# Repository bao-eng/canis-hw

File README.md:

# canis-hw
Isolated USB CAN-FD interface with SW-controllable termination resistors

## Features
- 2xCAN-FD interfaces supporting 8Mb/s
- 3kV isolation
- SW-controllable CAN-termination resistors
- 24V tolerant CAN transceivers and CAN termination circuit
- USB Type-C connector
- 2-layer PCB design
- Easy to solder 0603 components

## Firmware
Please use this candleLight_fw [fork](https://github.com/bao-eng/candleLight_fw/tree/canis)(canis branch). \
Prebuilt binary ```canis_fw.bin``` can be found in [releases](https://github.com/bao-eng/candleLight_fw/releases).
#### Flashing via DFU
- Short J2 pins ```1``` and ```2```
- Connect USB to the host PC
- Unshort J2
- In the ```lsusb``` output you should be able to see ```STMicroelectronics STM Device in DFU Mode```
- Run ```sudo dfu-util -d 0483:df11 -c 1 -i 0 -a 0 -s 0x08000000 -D canis_fw.bin```
- Reconnect USB
- In the ```lsusb``` output you should be able to see ```OpenMoko, Inc. Geschwister Schneider CAN adapter```
#### Flashing via SWD
- Connect ST-link to the J2
- Connect USB to the host PC
- Run ```st-flash write canis_fw.bin 0x08000000```
- Disconnect ST-link from J2
- Reconnect USB
- In the ```lsusb``` output you should be able to see ```OpenMoko, Inc. Geschwister Schneider CAN adapter```
## Usage
Bring up can0 interface and enable 120Ohm termination resistor:
```
ip link set can0 up type can bitrate 1000000 dbitrate 8000000 fd on termination 120
```
Disable 120Ohm termination resistor:
```
ip link set can0 type can termination 0
```

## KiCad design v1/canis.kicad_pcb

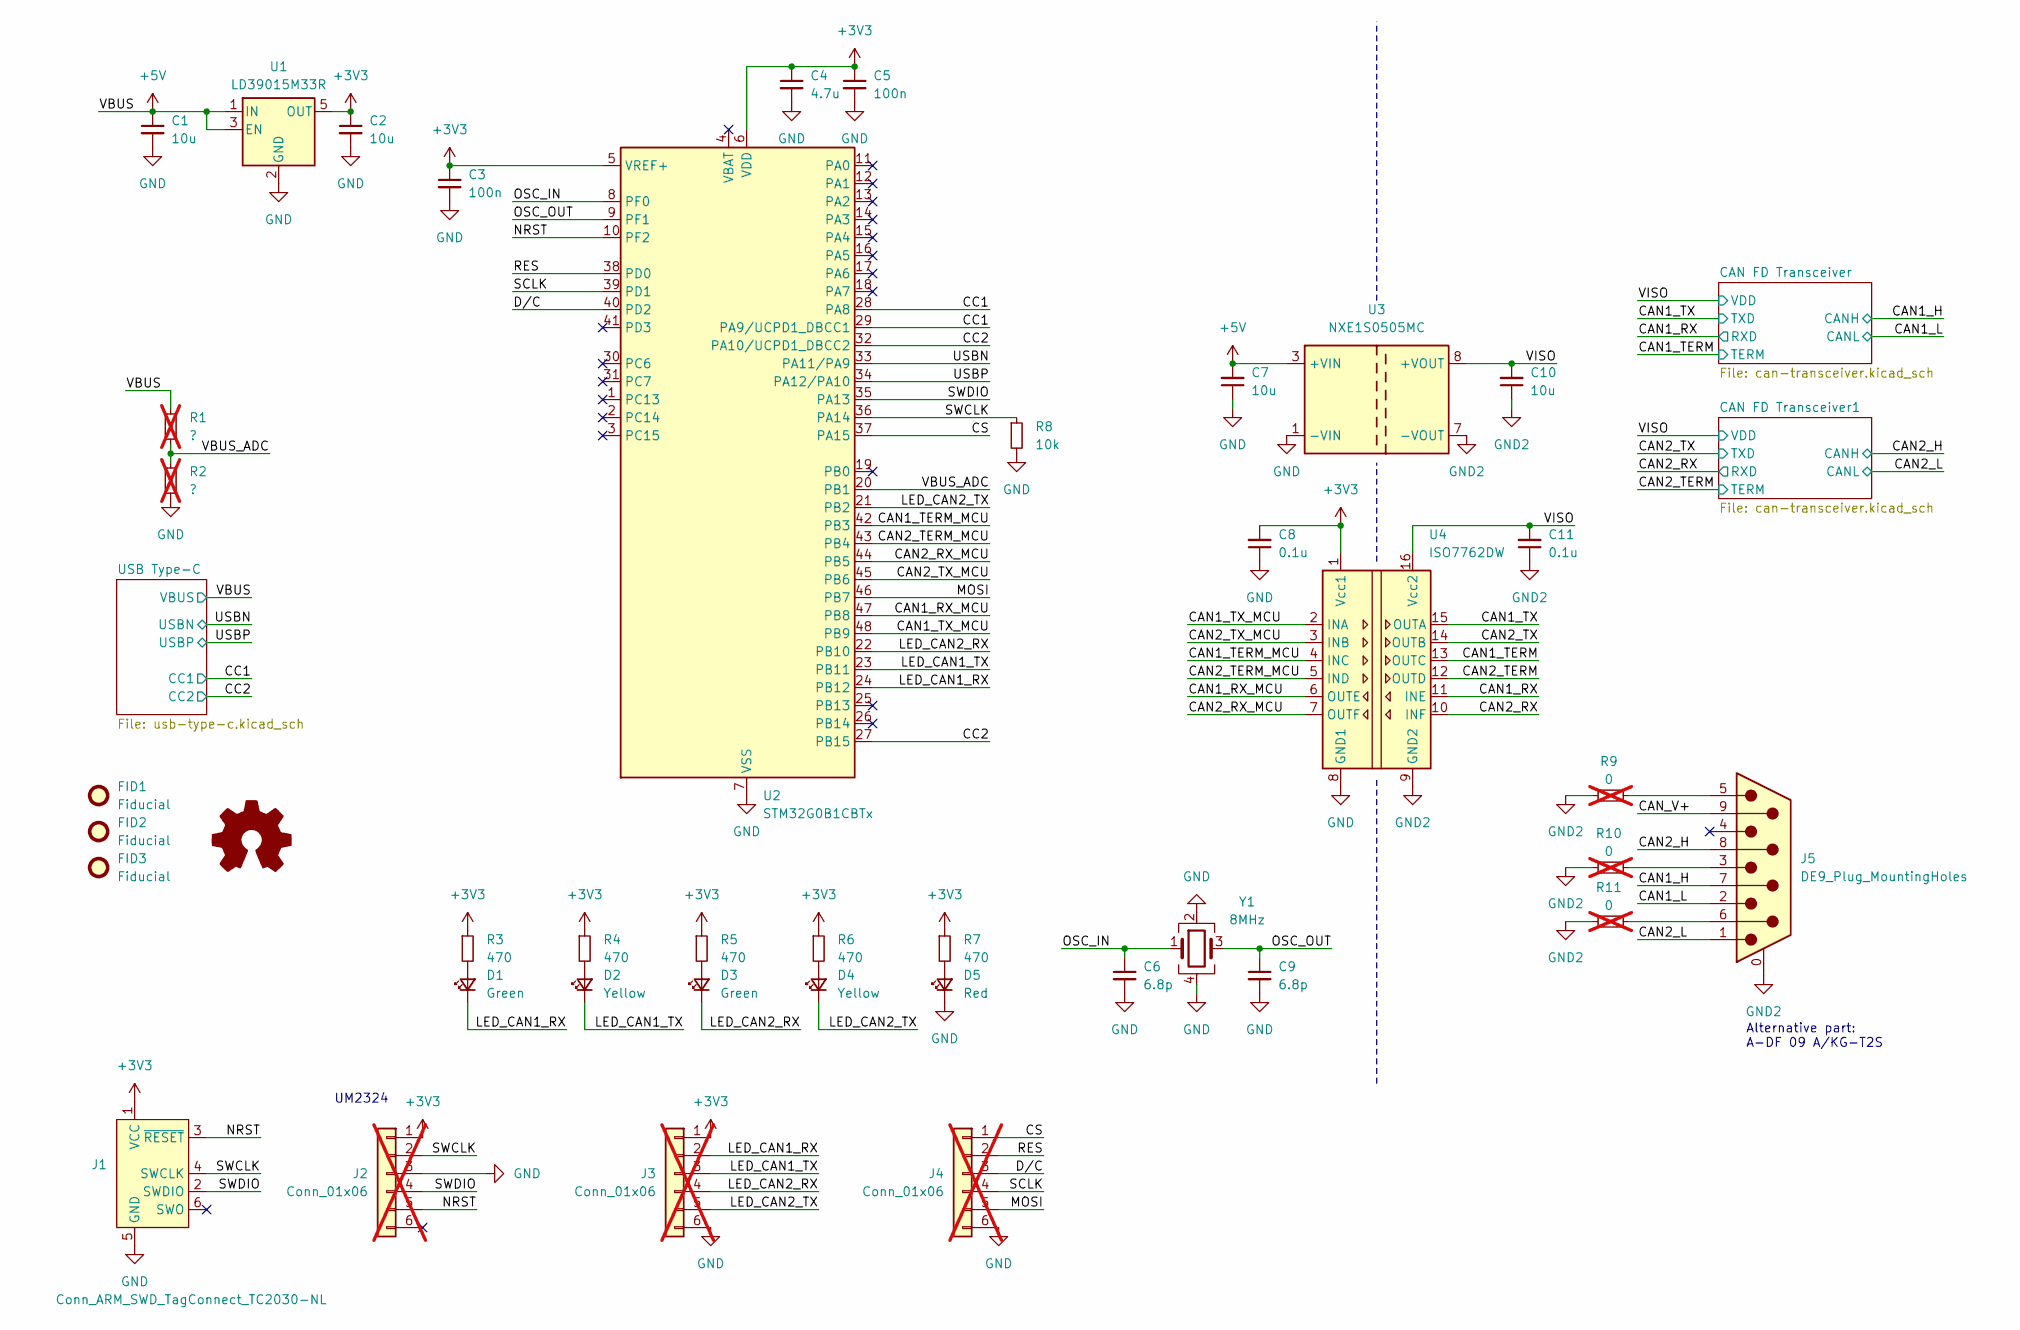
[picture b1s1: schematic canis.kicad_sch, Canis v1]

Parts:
C1, C2, C7, C10: 10u; C_0805_2012Metric; MPN 885012107010
C3, C5: 100n; C_0603_1608Metric; MPN 885012205018
C4: 4.7u; C_0603_1608Metric; MPN 885012106005
C6, C9: 6.8p; C_0603_1608Metric; MPN 885012006050
C8, C11: 0.1u; C_0603_1608Metric; MPN 885012205018
D1, D3: Green; LED_0603_1608Metric; MPN 150060VS75000
D2, D4: Yellow; LED_0603_1608Metric; MPN 150060YS75000
D5: Red; LED_0603_1608Metric; MPN 150060SS75000
FID1, FID2, FID3: Fiducial; Fiducial_1.5mm_Mask3mm
J1: Conn_ARM_SWD_TagConnect_TC2030-NL; Tag-Connect_TC2030-IDC-NL_2x03_P1.27mm_Vertical
J2, J3, J4: Conn_01x06; PinHeader_1x06_P2.54mm_Vertical; MPN 61300611121; not fitted
J5: DE9_Plug_MountingHoles; 618009231221; MPN 618009231221
R1, R2: ?; R_0603_1608Metric; not fitted
R3, R4, R5, R6, R7: 470; R_0603_1608Metric; MPN 560112116067
R8: 10k; R_0603_1608Metric; MPN 560112120019
R9, R10, R11: 0; R_0603_1608Metric; MPN 560112116001; not fitted
SYM1: Logo_Open_Hardware_Small; OSHW-Logo_5.7x6mm_SilkScreen
U1: LD39015M33R; SOT-23-5
U2: STM32G0B1CBTx; LQFP-48_7x7mm_P0.5mm
U3: NXE1S0505MC; Converter_DCDC_Murata_NXExSxxxxMC_SMD
U4: ISO7762DW; SOIC-16W_7.5x10.3mm_P1.27mm
Y1: 8MHz; Crystal_SMD_3225-4Pin_3.2x2.5mm; MPN 830108313809

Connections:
+3V3: C2.1, C3.1, C4.1, C5.1, C8.2, J1.1 (VCC), J2.1, J3.1, R3.1, R4.1, R5.1, R6.1, R7.1, U1.5 (OUT), U2.5 (VREF+), U2.6 (VDD), U4.1 (Vcc1)
+5V: C1.1, C7.2, R1.1, U1.1 (IN), U1.3 (EN), U3.3 (+VIN); also elsewhere on the board
/CAN1_H: J5.7; also elsewhere on the board
/CAN1_L: J5.2; also elsewhere on the board
/CAN1_RX: U4.11 (INE); also elsewhere on the board
/CAN1_RX_MCU: U2.47 (PB8), U4.6 (OUTE)
/CAN1_TERM: U4.13 (OUTC); also elsewhere on the board
/CAN1_TERM_MCU: U2.42 (PB3), U4.4 (INC)
/CAN1_TX: U4.15 (OUTA); also elsewhere on the board
/CAN1_TX_MCU: U2.48 (PB9), U4.2 (INA)
/CAN2_H: J5.8; also elsewhere on the board
/CAN2_L: J5.1; also elsewhere on the board
/CAN2_RX: U4.10 (INF); also elsewhere on the board
/CAN2_RX_MCU: U2.44 (PB5), U4.7 (OUTF)
/CAN2_TERM: U4.12 (OUTD); also elsewhere on the board
/CAN2_TERM_MCU: U2.43 (PB4), U4.5 (IND)
/CAN2_TX: U4.14 (OUTB); also elsewhere on the board
/CAN2_TX_MCU: U2.45 (PB6), U4.3 (INB)
/CAN_V+: J5.9
/CC1: U2.28 (PA8), U2.29 (PA9/UCPD1_DBCC1); also elsewhere on the board
/CC2: U2.27 (PB15), U2.32 (PA10/UCPD1_DBCC2); also elsewhere on the board
/CS: J4.1, U2.37 (PA15)
/D/C: J4.3, U2.40 (PD2)
/LED_CAN1_RX: D1.1 (K), J3.2, U2.24 (PB12)
/LED_CAN1_TX: D2.1 (K), J3.3, U2.23 (PB11)
/LED_CAN2_RX: D3.1 (K), J3.4, U2.22 (PB10)
/LED_CAN2_TX: D4.1 (K), J3.5, U2.21 (PB2)
/MOSI: J4.5, U2.46 (PB7)
/NRST: J1.3 (~RESET), J2.5, U2.10 (PF2)
/OSC_IN: C6.1, U2.8 (PF0), Y1.1
/OSC_OUT: C9.1, U2.9 (PF1), Y1.3
/RES: J4.2, U2.38 (PD0)
/SCLK: J4.4, U2.39 (PD1)
/SWCLK: J1.4 (SWCLK), J2.2, R8.1, U2.36 (PA14)
/SWDIO: J1.2 (SWDIO), J2.4, U2.35 (PA13)
/USBN: U2.33 (PA11/PA9); also elsewhere on the board
/USBP: U2.34 (PA12/PA10); also elsewhere on the board
/VBUS_ADC: R1.2, R2.1, U2.20 (PB1)
/VISO: C10.2, C11.2, U3.8 (+VOUT), U4.16 (Vcc2); also elsewhere on the board
GND: C1.2, C2.2, C3.2, C4.2, C5.2, C6.2, C7.1, C8.1, C9.2, D5.1 (K), J1.5 (GND), J2.3, J3.6, J4.6, R2.2, R8.2, U1.2 (GND), U2.7 (VSS), U3.1 (-VIN), U4.8 (GND1), Y1.2, Y1.4; also elsewhere on the board
GND2: C10.1, C11.1, J5.0 (PAD), R9.1, R10.1, R11.1, U3.7 (-VOUT), U4.9 (GND2); also elsewhere on the board
unnamed: D1.2 (A), R3.2
unnamed: D2.2 (A), R4.2
unnamed: D3.2 (A), R5.2
unnamed: D4.2 (A), R6.2
unnamed: D5.2 (A), R7.2
unnamed: J5.3, R10.2
unnamed: J5.5, R9.2
unnamed: J5.6, R11.2

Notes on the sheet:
UM2324
Alternative part: A-DF 09 A/KG-T2S

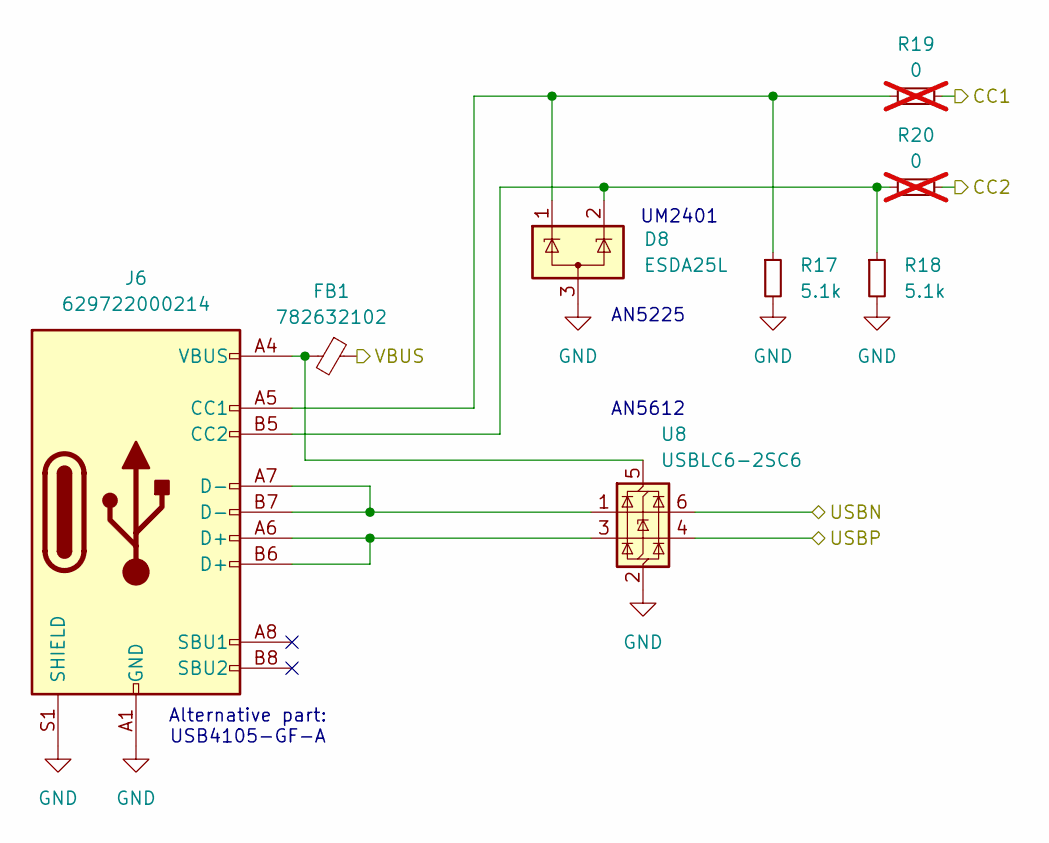
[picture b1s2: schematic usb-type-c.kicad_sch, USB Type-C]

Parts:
D8: ESDA25L; SOT-23-3
FB1: 782632102; L_0603_1608Metric
J6: 629722000214
R17, R18: 5.1k; R_0805_2012Metric; MPN 560112120019
R19, R20: 0; R_0603_1608Metric; MPN 560112116001; not fitted
U8: USBLC6-2SC6; SOT-23-6

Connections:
+5V: FB1.1; also elsewhere on the board
/CC1: R19.2; also elsewhere on the board
/CC2: R20.2; also elsewhere on the board
/USBN: U8.6 (I/O1); also elsewhere on the board
/USBP: U8.4 (I/O2); also elsewhere on the board
GND: D8.3 (A), J6.A1 (GND), J6.A12 (GND), J6.B1 (GND), J6.B12 (GND), J6.S1 (SHIELD), R17.2, R18.2, U8.2 (GND); also elsewhere on the board
unnamed: D8.1 (K), J6.A5 (CC1), R17.1, R19.1
unnamed: D8.2 (K), J6.B5 (CC2), R18.1, R20.1
unnamed: J6.A6 (D+), J6.B6 (D+), U8.3 (I/O2)
unnamed: J6.A7 (D-), J6.B7 (D-), U8.1 (I/O1)
unnamed: FB1.2, J6.A4 (VBUS), J6.A9 (VBUS), J6.B4 (VBUS), J6.B9 (VBUS), U8.5 (VBUS)

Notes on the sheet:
UM2401
AN5225
AN5612
Alternative part: USB4105-GF-A

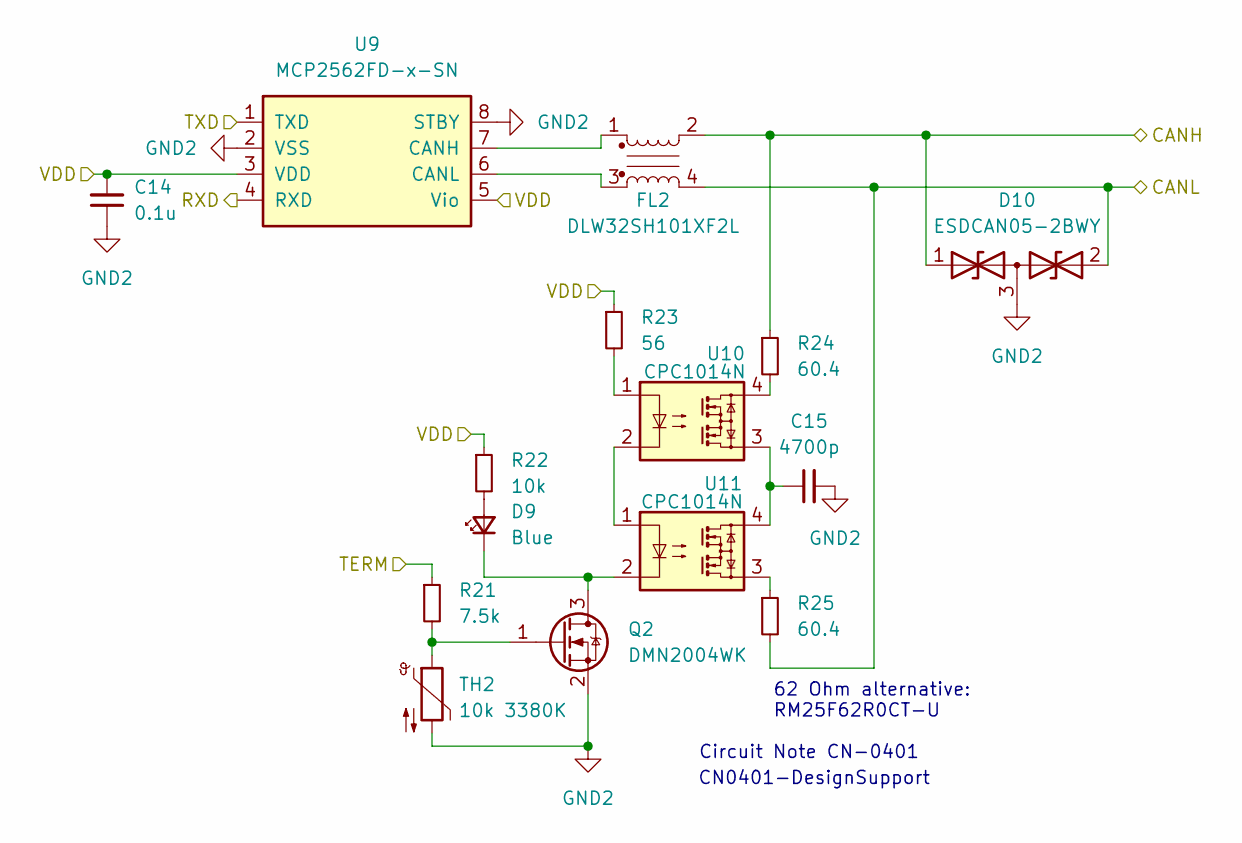
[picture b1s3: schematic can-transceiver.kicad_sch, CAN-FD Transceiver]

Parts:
C14: 0.1u; C_0603_1608Metric; MPN 885012205018
C15: 4700p; C_0805_2012Metric; MPN 885012207090
D9: Blue; LED_0603_1608Metric; MPN 150060BS75000
D10: ESDCAN05-2BWY; SOT-323_SC-70
FL2: DLW32SH101XF2L
Q2: DMN2004WK; SOT-323_SC-70
R21: 7.5k; R_0603_1608Metric; MPN 560112116005
R22: 10k; R_0603_1608Metric; MPN 560112116005
R23: 56; R_1206_3216Metric; MPN RC1206FR-0756RL
R24, R25: 60.4; R_2512_6332Metric; MPN 3504G3A60R4FTDF
TH2: 10k 3380K; R_0603_1608Metric; MPN NCU18XH103F6SRB
U9: MCP2562FD-x-SN; SOIC-8_3.9x4.9mm_P1.27mm
U10, U11: CPC1014N; SOP-4_3.8x4.1mm_P2.54mm

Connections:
/CAN2_H: D10.1 (A1), FL2.2, R24.1; also elsewhere on the board
/CAN2_L: D10.2 (A2), FL2.4, R25.2; also elsewhere on the board
/CAN2_RX: U9.4 (RXD); also elsewhere on the board
/CAN2_TERM: R21.1; also elsewhere on the board
/CAN2_TX: U9.1 (TXD); also elsewhere on the board
/VISO: C14.2, R22.1, R23.1, U9.3 (VDD), U9.5 (Vio); also elsewhere on the board
GND2: C14.1, C15.2, D10.3 (common), Q2.2 (S), TH2.2, U9.2 (VSS), U9.8 (STBY); also elsewhere on the board
unnamed: C15.1, U10.3, U11.4
unnamed: D9.2 (A), R22.2
unnamed: D9.1 (K), Q2.3 (D), U11.2
unnamed: Q2.1 (G), R21.2, TH2.1
unnamed: R23.2, U10.1
unnamed: R24.2, U10.4
unnamed: R25.1, U11.3
unnamed: FL2.1, U9.7 (CANH)
unnamed: FL2.3, U9.6 (CANL)
unnamed: U10.2, U11.1

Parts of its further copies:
C12: 0.1u; C_0603_1608Metric; MPN 885012205018
C13: 4700p; C_0805_2012Metric; MPN 885012207090
D6: Blue; LED_0603_1608Metric; MPN 150060BS75000
D7: ESDCAN05-2BWY; SOT-323_SC-70
FL1: DLW32SH101XF2L
Q1: DMN2004WK; SOT-323_SC-70
R12: 7.5k; R_0603_1608Metric; MPN 560112116005
R13: 10k; R_0603_1608Metric; MPN 560112116005
R14: 56; R_1206_3216Metric; MPN RC1206FR-0756RL
R15, R16: 60.4; R_2512_6332Metric; MPN 3504G3A60R4FTDF
TH1: 10k 3380K; R_0603_1608Metric; MPN NCU18XH103F6SRB
U5: MCP2562FD-x-SN; SOIC-8_3.9x4.9mm_P1.27mm
U6, U7: CPC1014N; SOP-4_3.8x4.1mm_P2.54mm

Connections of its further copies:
/CAN1_H: D7.1 (A1), FL1.2, R15.1; also elsewhere on the board
/CAN1_L: D7.2 (A2), FL1.4, R16.2; also elsewhere on the board
/CAN1_RX: U5.4 (RXD); also elsewhere on the board
/CAN1_TERM: R12.1; also elsewhere on the board
/CAN1_TX: U5.1 (TXD); also elsewhere on the board
/VISO: C12.2, R13.1, R14.1, U5.3 (VDD), U5.5 (Vio); also elsewhere on the board
GND2: C12.1, C13.2, D7.3 (common), Q1.2 (S), TH1.2, U5.2 (VSS), U5.8 (STBY); also elsewhere on the board
unnamed: C13.1, U6.3, U7.4
unnamed: D6.2 (A), R13.2
unnamed: D6.1 (K), Q1.3 (D), U7.2
unnamed: Q1.1 (G), R12.2, TH1.1
unnamed: R14.2, U6.1
unnamed: R15.2, U6.4
unnamed: R16.1, U7.3
unnamed: FL1.1, U5.7 (CANH)
unnamed: FL1.3, U5.6 (CANL)
unnamed: U6.2, U7.1

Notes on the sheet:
CN0401-DesignSupport
62 Ohm alternative: RM25F62R0CT-U
Circuit Note CN-0401

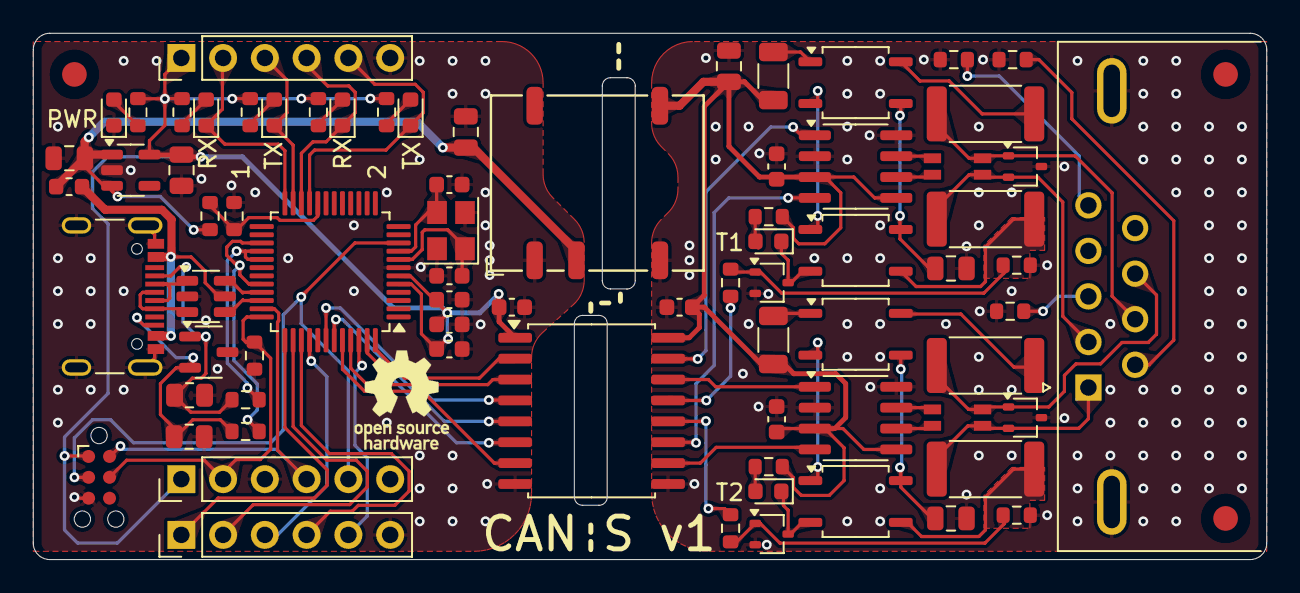
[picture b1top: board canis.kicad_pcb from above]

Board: 2 copper layers, 75.0 x 32.0 mm, 79 parts (0 on the bottom side), 73 nets.
